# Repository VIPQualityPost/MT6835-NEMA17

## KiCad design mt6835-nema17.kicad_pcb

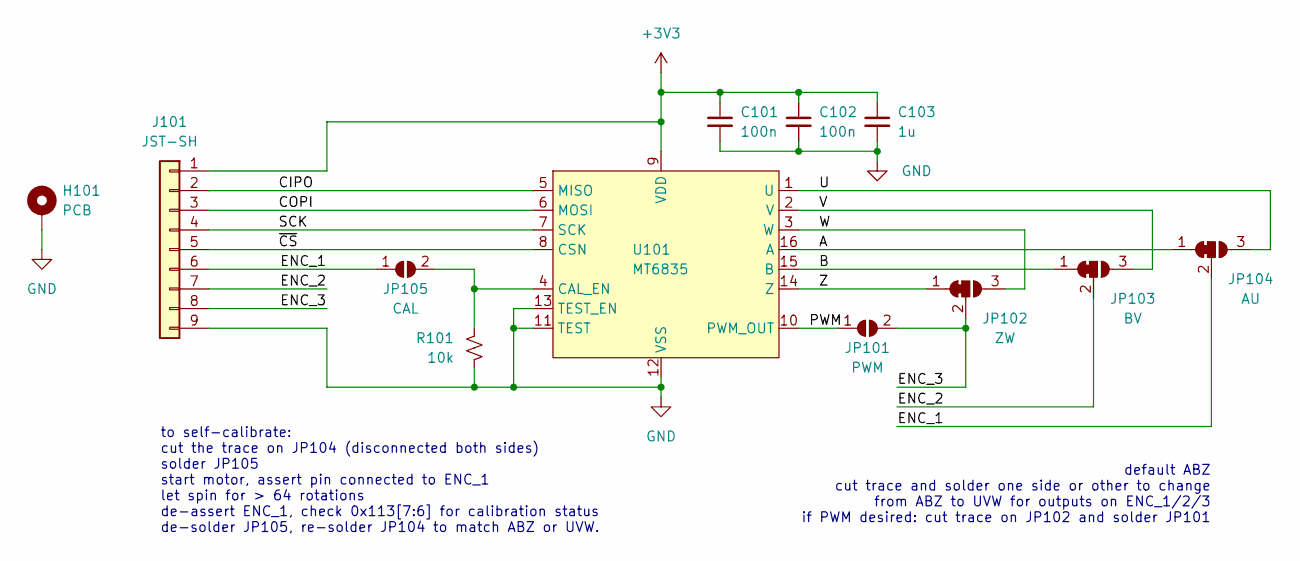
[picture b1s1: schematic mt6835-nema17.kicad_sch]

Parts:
C101, C102: 100n; C_0402_1005Metric; JLCPCB Part # C307331
C103: 1u; C_0402_1005Metric; JLCPCB Part # C52923
H101: PCB; NEMA17
J101: JST-SH; CONN-SMD_AFC10-S09QCC-00; JLCPCB Part # C2764188
JP101: PWM; SolderJumper-2_P1.3mm_Open_RoundedPad1.0x1.5mm
JP102: ZW; SolderJumper-3_P1.3mm_Bridged12_RoundedPad1.0x1.5mm
JP103: BV; SolderJumper-3_P1.3mm_Bridged12_RoundedPad1.0x1.5mm
JP104: AU; SolderJumper-3_P1.3mm_Bridged12_RoundedPad1.0x1.5mm
JP105: CAL; SolderJumper-2_P1.3mm_Open_RoundedPad1.0x1.5mm
R101: 10k; R_0402_1005Metric; JLCPCB Part # C25744
U101: MT6835; MagnTek TSSOP-16-1EP_4.4x5mm_P0.65mm; JLCPCB Part # C2932578

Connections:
+3V3: C101.1, C102.1, C103.1, J101.1, U101.9 (VDD)
/A: JP104.1 (A), U101.16 (A)
/B: JP103.1 (A), U101.15 (B)
/CIPO: J101.2, U101.5 (MISO)
/COPI: J101.3, U101.6 (MOSI)
/ENC_1: J101.6, JP104.2 (C), JP105.1 (A)
/ENC_2: J101.7, JP103.2 (C)
/ENC_3: J101.8, JP101.2 (B), JP102.2 (C)
/PWM: JP101.1 (A), U101.10 (PWM_OUT)
/SCK: J101.4, U101.7 (SCK)
/U: JP104.3 (B), U101.1 (U)
/V: JP103.3 (B), U101.2 (V)
/W: JP102.3 (B), U101.3 (W)
/Z: JP102.1 (A), U101.14 (Z)
/~CS: J101.5, U101.8 (CSN)
GND: C101.2, C102.2, C103.2, H101.1, J101.9, R101.2, U101.11 (TEST), U101.12 (VSS), U101.13 (TEST_EN)
unnamed: JP105.2 (B), R101.1, U101.4 (CAL_EN)

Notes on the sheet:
default ABZ cut trace and solder one side or other to change from ABZ to UVW for outputs on ENC_1/2/3 if PWM desired: cut trace on JP102 and solder JP101
to self-calibrate: cut the trace on JP104 (disconnected both sides) solder JP105 start motor, assert pin connected to ENC_1 let spin for > 64 rotations de-assert ENC_1, check 0x113[7:6] for calibration status de-solder JP105, re-solder JP104 to match ABZ or UVW.

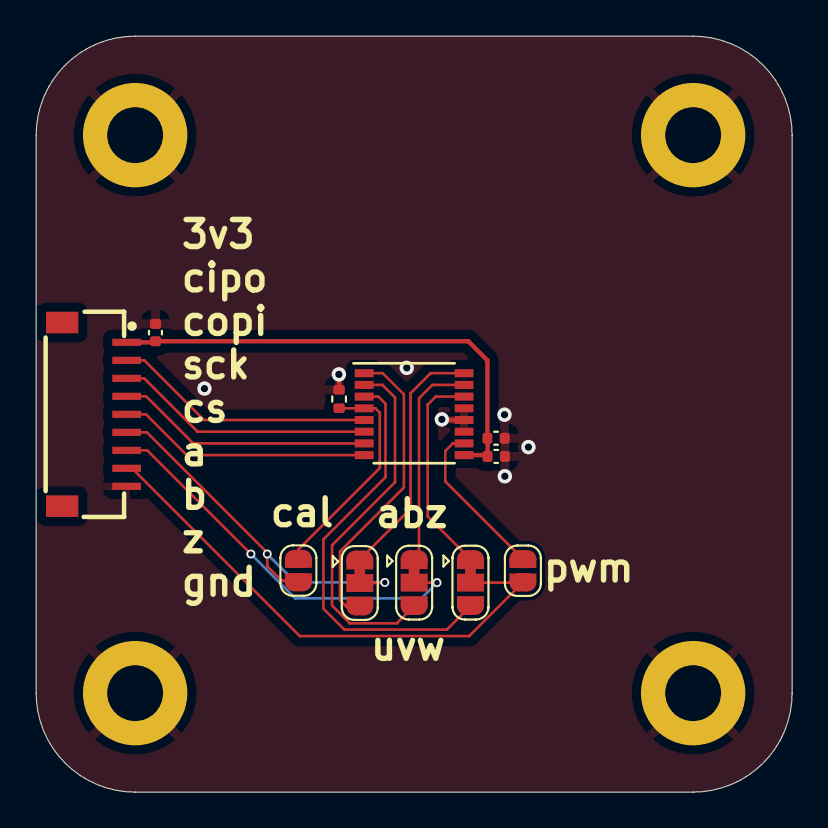
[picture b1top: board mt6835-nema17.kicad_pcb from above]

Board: 2 copper layers, 42.0 x 42.0 mm, 12 parts (0 on the bottom side), 17 nets.

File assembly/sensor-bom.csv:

Designator,Comment,Footprint,JLCPCB Part #
"C101, C102",100n,0402,C307331
C103,1u,0403,C52923
R101,10k,0404,C25744
U101,MT6835,TSSOP-16,C2932578
J101,JST-SH,,C2764188
